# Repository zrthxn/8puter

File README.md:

# 8puter

This is a Homebrew 8-bit computer project, using mostly simple modern parts.
Based on the legendary MOS6502 processor, we are using the modern CMOS version made by WDC. Basically an exercise in computer architechture. I plan to get this manufactured into a PCB and assemble myself into a working computer. 

Please feel free to leave reviews/sanity checks from people who have done this sort of thing before, or know something about this, in the [issues](/issues).  

## Preview

Here is a picture of a 3D model of the completed PCB.

<p align="center" style="text-align: center; font-size: larger; font-weight: 600;">
// 
<a href="plots/8puter.pdf">Schematic</a> / 
<a href="plots/8puter.csv">Bill of Materials</a> 
//
</p>

## My Goals

The main thing I want to be able to do with this SBC is to program it with itself. This means having some way to input text from a keyboard and display it to some kind of screen/output device, and I've chosen a VGA monitor for this. I'm not trying to keep this compatible with the ROMs/BIOSs or code of old but I want to be able to write my own, preferably on the machine itself. 
Also, I dont want to use discrete logic for everything since I have some experience with trying to make that work. I'm also not necessarily using all DIP chips because of lack space, and going SMD isnt that much of a problem.

To store programs on a sort of "disk", I thought I need to add some sort of serial interface which can talk to a microSD card, such that the computer can use it as storage. This is accomplished via SPI. 
The peripheral interface talks to a USB controller and *should* be able to use a USB keyboard as input device. This idea was taken from the schematic of the [SBC dev board that WDC sells](https://wdc65xx.com/Single-Board-Computers/w65c02sxb/).

The video signal is being generated by a microcontroller because I thought that's probably the easiest way to get it working without worrying about a lot of VGA signal timing. This MCU is fast enough to generate a 640x480 screen and has enough memory to store the framebuffer and its the only *cheat* I've used. Some more details are in my schematic

### Main Parts

**uProcessor:** W65C02S  
**ROM and RAM:** AT28C256 and AS6C62256, both 32K  
**VIA:** W65C22  
**USB I/f:** FT245RL  
**Video:** PIC32MX270 uController

## Manufacturing

So after quite a while, I have finally got this PCB manufactured and it came out better than I had imagined.
I was having trouble finding a local PCB maker who had the right capabilities and would manufacture this board at a small scale. 
Then I found Robu.in and their manufacturing service. I'm not sure if they've been doing this for a while but I never knew about them.

The board files are ready to send to a manufacturer of your choice as they are. You can find the gerbers in a ZIP and just fire them off. 
I recommend Robu.in if you're in India. Otherwise I'd recommend PCBWay.com

See the [Releases](https://github.com/zrthxn/8puter/releases) for updates.

## Resources

Some great resources I found for this project, including those from people who have done this sort of thing before.

- [Ben Eater's Excellent Videos](https://www.youtube.com/watch?v=LnzuMJLZRdU&list=PLowKtXNTBypFbtuVMUVXNR0z1mu7dp7eH)
- [George Foot's videos](https://www.youtube.com/watch?v=EC1Ous1zT5w&list=PLWKtKD_FaUF6IsFc1maERpOwWM2hrOM3b)
- [forum.6502.org](http://forum.6502.org/)
- [WDC's own SBC board schematic](https://wdc65xx.com/Single-Board-Computers/w65c02sxb/)
- [6052 Primer](http://wilsonminesco.com/6502primer) on how to get started building your own, especially the [address decode](http://wilsonminesco.com/6502primer/addr_decoding.html) section
- [6502.org: Homebuilt Projects](http://www.6502.org/homebuilt)
- [This guy's breadboard computer](https://www.youtube.com/watch?v=sdFXc0Rkpvc&list=PLdGm_pyUmoII9D16mzw-XsJjHKi3f1kqT) which is based on the (later) 65816 processor, but has some great ideas.

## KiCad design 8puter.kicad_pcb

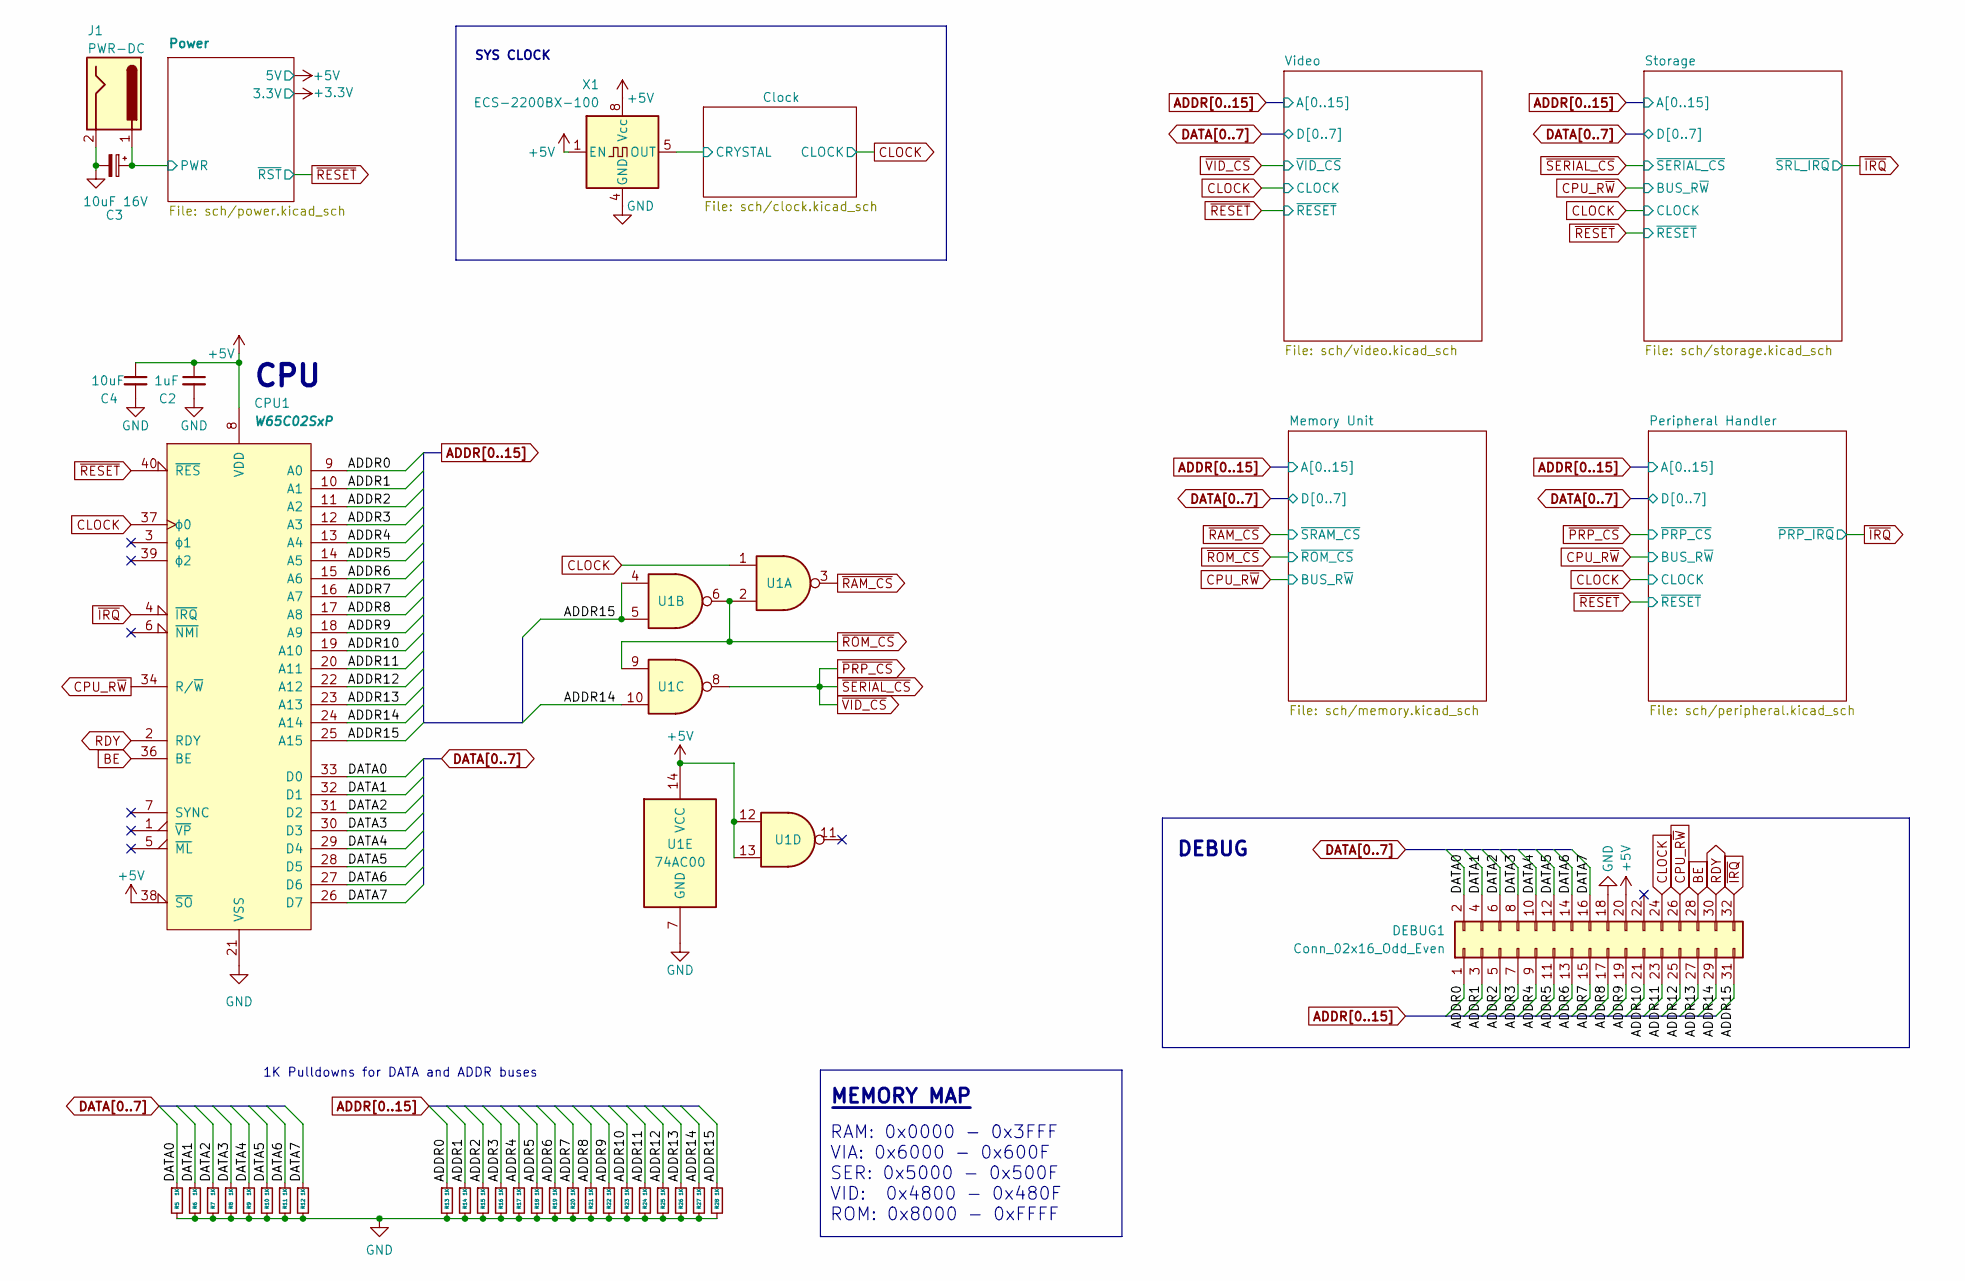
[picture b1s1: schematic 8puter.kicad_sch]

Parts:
C2: 1uF; C_0805_2012Metric
C3: 10uF 16V; CP_Radial_D5.0mm_P2.50mm
C4: 10uF; C_0805_2012Metric
CPU1: W65C02SxP; DIP-40_W15.24mm_LongPads
DEBUG1: Conn_02x16_Odd_Even; PinHeader_2x16_P2.54mm_Vertical
J1: PWR-DC; BarrelJack_CUI_PJ-063AH_Horizontal
R5, R6, R7, R8, R9, R10, R11, R12, R13, R14, R15, R16, R17, R18, R19, R20, R21, R22, R23, R24, R25, R26, R27, R28: 1K; R_0805_2012Metric
U1: 74AC00; TSSOP-14_4.4x5mm_P0.65mm
X1: ECS-2200BX-100; Oscillator_DIP-8

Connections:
+5V: C2.1, C4.1, CPU1.8 (VDD), CPU1.38 (~SO), DEBUG1.20, U1.12, U1.13, U1.14 (VCC), X1.1 (EN), X1.8 (Vcc); also elsewhere on the board
/Clock/CRYSTAL: X1.5 (OUT); also elsewhere on the board
/Power/PWR: C3.1, J1.1; also elsewhere on the board
ADDR0: CPU1.9 (A0), DEBUG1.1, R13.1; also elsewhere on the board
ADDR1: CPU1.10 (A1), DEBUG1.3, R14.1; also elsewhere on the board
ADDR2: CPU1.11 (A2), DEBUG1.5, R15.1; also elsewhere on the board
ADDR3: CPU1.12 (A3), DEBUG1.7, R16.1; also elsewhere on the board
ADDR4: CPU1.13 (A4), DEBUG1.9, R17.1; also elsewhere on the board
ADDR5: CPU1.14 (A5), DEBUG1.11, R18.1; also elsewhere on the board
ADDR6: CPU1.15 (A6), DEBUG1.13, R19.1; also elsewhere on the board
ADDR7: CPU1.16 (A7), DEBUG1.15, R20.1; also elsewhere on the board
ADDR8: CPU1.17 (A8), DEBUG1.17, R21.1; also elsewhere on the board
ADDR9: CPU1.18 (A9), DEBUG1.19, R22.1; also elsewhere on the board
ADDR10: CPU1.19 (A10), DEBUG1.21, R23.1; also elsewhere on the board
ADDR11: CPU1.20 (A11), DEBUG1.23, R24.1; also elsewhere on the board
ADDR12: CPU1.22 (A12), DEBUG1.25, R25.1; also elsewhere on the board
ADDR13: CPU1.23 (A13), DEBUG1.27, R26.1; also elsewhere on the board
ADDR14: CPU1.24 (A14), DEBUG1.29, R27.1, U1.10; also elsewhere on the board
ADDR15: CPU1.25 (A15), DEBUG1.31, R28.1, U1.4, U1.5
BE: CPU1.36 (BE), DEBUG1.28
CLOCK: CPU1.37 (ϕ0), DEBUG1.24, U1.1; also elsewhere on the board
CPU_R~W: CPU1.34 (R/~W), DEBUG1.26; also elsewhere on the board
DATA0: CPU1.33 (D0), DEBUG1.2, R5.1; also elsewhere on the board
DATA1: CPU1.32 (D1), DEBUG1.4, R6.1; also elsewhere on the board
DATA2: CPU1.31 (D2), DEBUG1.6, R7.1; also elsewhere on the board
DATA3: CPU1.30 (D3), DEBUG1.8, R8.1; also elsewhere on the board
DATA4: CPU1.29 (D4), DEBUG1.10, R9.1; also elsewhere on the board
DATA5: CPU1.28 (D5), DEBUG1.12, R10.1; also elsewhere on the board
DATA6: CPU1.27 (D6), DEBUG1.14, R11.1; also elsewhere on the board
DATA7: CPU1.26 (D7), DEBUG1.16, R12.1; also elsewhere on the board
RDY: CPU1.2 (RDY), DEBUG1.30
~IRQ: CPU1.4 (~IRQ), DEBUG1.32; also elsewhere on the board
~PRP_CS: U1.8; also elsewhere on the board
~RAM_CS: U1.3; also elsewhere on the board
~RESET: CPU1.40 (~RES); also elsewhere on the board
~ROM_CS: U1.2, U1.6, U1.9; also elsewhere on the board

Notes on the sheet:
SYS CLOCK
DEBUG
RAM: 0x0000 - 0x3FFF VIA: 0x6000 - 0x600F SER: 0x5000 - 0x500F VID: 0x4800 - 0x480F ROM: 0x8000 - 0xFFFF
MEMORY MAP ~{ }
1K Pulldowns for DATA and ADDR buses
CPU

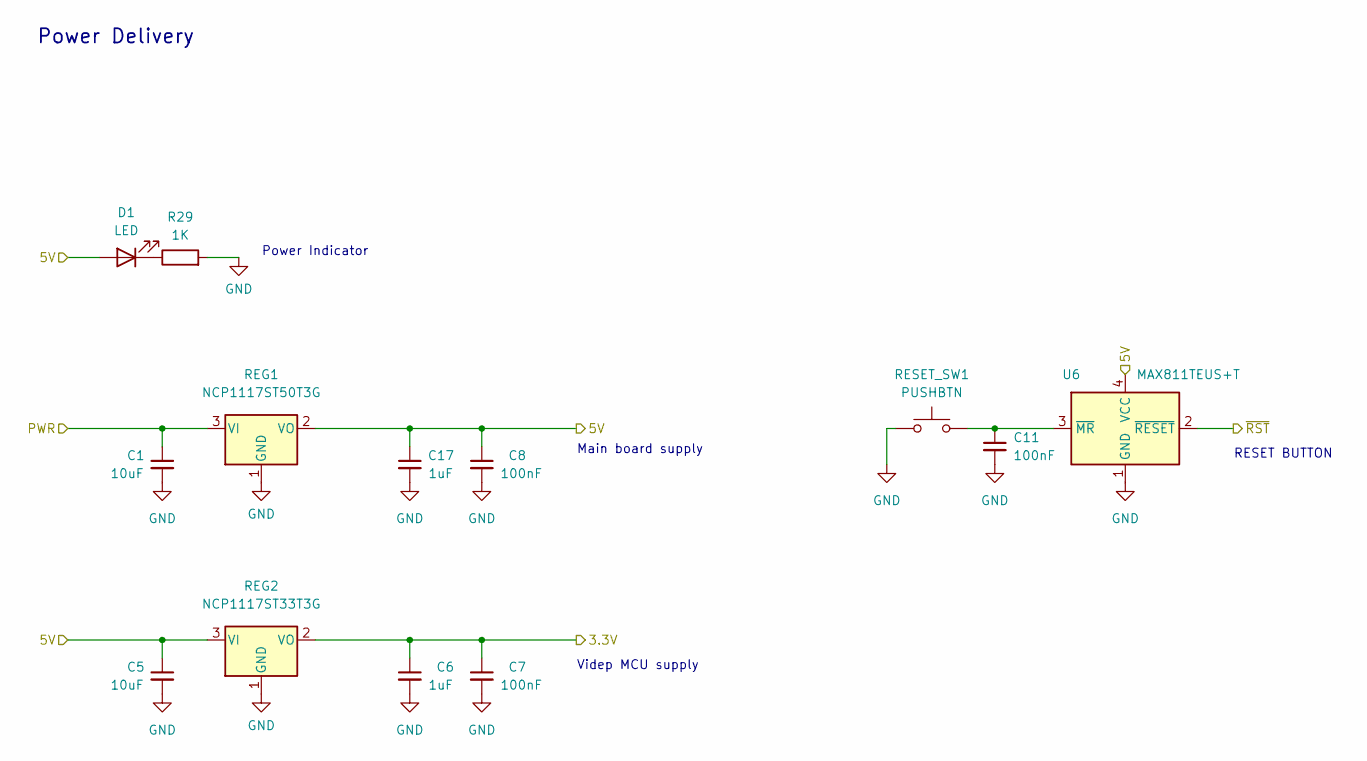
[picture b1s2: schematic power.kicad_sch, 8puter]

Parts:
C1, C5: 10uF; C_0805_2012Metric
C6, C17: 1uF; C_0805_2012Metric
C7, C8, C11: 100nF; C_0805_2012Metric
D1: LED; LED_0805_2012Metric
R29: 1K; R_0805_2012Metric
REG1: NCP1117ST50T3G; SOT-223-3_TabPin2
REG2: NCP1117ST33T3G; SOT-223-3_TabPin2
RESET_SW1: PUSHBTN; SW_PUSH_6mm_H13mm
U6: MAX811TEUS+T; SOT-143

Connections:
+3V3: C6.1, C7.1, REG2.2 (VO); also elsewhere on the board
+5V: C5.1, C8.1, C17.1, D1.2 (A), REG1.2 (VO), REG2.3 (VI), U6.4 (VCC); also elsewhere on the board
/Power/PWR: C1.1, REG1.3 (VI); also elsewhere on the board
unnamed: C11.1, RESET_SW1.2, U6.3 (~MR)
unnamed: D1.1 (K), R29.1
~RESET: U6.2 (~RESET); also elsewhere on the board

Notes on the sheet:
Power Delivery
RESET BUTTON
Videp MCU supply
Power Indicator
Main board supply

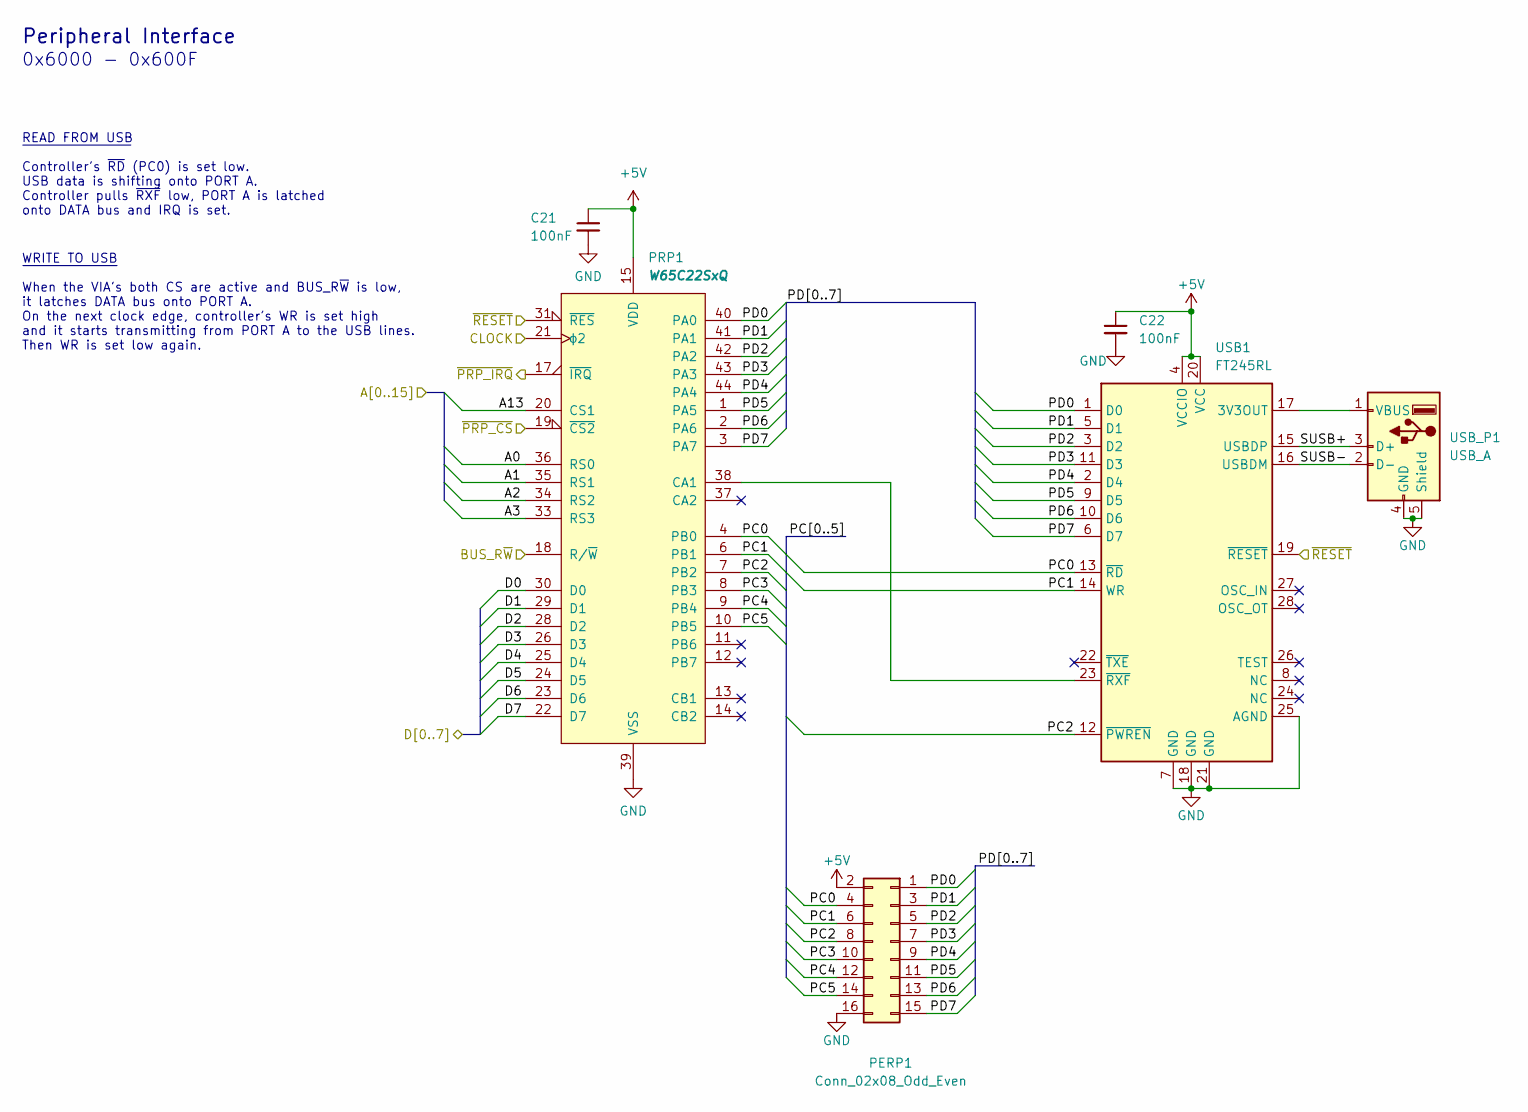
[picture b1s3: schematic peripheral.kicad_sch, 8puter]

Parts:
C21, C22: 100nF; C_0805_2012Metric
PERP1: Conn_02x08_Odd_Even; PinHeader_2x08_P2.54mm_Vertical
PRP1: W65C22SxQ; PQFP-44_10x10mm_P0.8mm
USB1: FT245RL; SSOP-28_5.3x10.2mm_P0.65mm
USB_P1: USB_A; USB_A_TE_292303-7_Horizontal

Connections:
+5V: C21.1, C22.1, PERP1.2, PRP1.15 (VDD), USB1.4 (VCCIO), USB1.20 (VCC); also elsewhere on the board
/Peripheral Handler/PC0: PERP1.4, PRP1.4 (PB0), USB1.13 (~RD)
/Peripheral Handler/PC1: PERP1.6, PRP1.6 (PB1), USB1.14 (WR)
/Peripheral Handler/PC2: PERP1.8, PRP1.7 (PB2), USB1.12 (~PWREN)
/Peripheral Handler/PC3: PERP1.10, PRP1.8 (PB3)
/Peripheral Handler/PC4: PERP1.12, PRP1.9 (PB4)
/Peripheral Handler/PC5: PERP1.14, PRP1.10 (PB5)
/Peripheral Handler/PD0: PERP1.1, PRP1.40 (PA0), USB1.1 (D0)
/Peripheral Handler/PD1: PERP1.3, PRP1.41 (PA1), USB1.5 (D1)
/Peripheral Handler/PD2: PERP1.5, PRP1.42 (PA2), USB1.3 (D2)
/Peripheral Handler/PD3: PERP1.7, PRP1.43 (PA3), USB1.11 (D3)
/Peripheral Handler/PD4: PERP1.9, PRP1.44 (PA4), USB1.2 (D4)
/Peripheral Handler/PD5: PERP1.11, PRP1.1 (PA5), USB1.9 (D5)
/Peripheral Handler/PD6: PERP1.13, PRP1.2 (PA6), USB1.10 (D6)
/Peripheral Handler/PD7: PERP1.15, PRP1.3 (PA7), USB1.6 (D7)
/Peripheral Handler/SUSB+: USB1.15 (USBDP), USB_P1.3 (D+)
/Peripheral Handler/SUSB-: USB1.16 (USBDM), USB_P1.2 (D-)
ADDR0: PRP1.36 (RS0); also elsewhere on the board
ADDR1: PRP1.35 (RS1); also elsewhere on the board
ADDR2: PRP1.34 (RS2); also elsewhere on the board
ADDR3: PRP1.33 (RS3); also elsewhere on the board
ADDR13: PRP1.20 (CS1); also elsewhere on the board
CLOCK: PRP1.21 (ϕ2); also elsewhere on the board
CPU_R~W: PRP1.18 (R/~W); also elsewhere on the board
DATA0: PRP1.30 (D0); also elsewhere on the board
DATA1: PRP1.29 (D1); also elsewhere on the board
DATA2: PRP1.28 (D2); also elsewhere on the board
DATA3: PRP1.26 (D3); also elsewhere on the board
DATA4: PRP1.25 (D4); also elsewhere on the board
DATA5: PRP1.24 (D5); also elsewhere on the board
DATA6: PRP1.23 (D6); also elsewhere on the board
DATA7: PRP1.22 (D7); also elsewhere on the board
unnamed: PRP1.38 (CA1), USB1.23 (~RXF)
unnamed: USB1.17 (3V3OUT), USB_P1.1 (VBUS)
~IRQ: PRP1.17 (~IRQ); also elsewhere on the board
~PRP_CS: PRP1.19 (~CS2); also elsewhere on the board
~RESET: PRP1.31 (~RES), USB1.19 (~RESET); also elsewhere on the board

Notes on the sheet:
0x6000 - 0x600F
Peripheral Interface
WRITE TO USB ~{ } When the VIA's both CS are active and BUS_R~{W} is low, it latches DATA bus onto PORT A. On the next clock edge, controller's WR is set high and it starts transmitting from PORT A to the USB lines. Then WR is set low again.
READ FROM USB ~{ } Controller's ~{RD} (PC0) is set low. USB data is shifting onto PORT A. Controller pulls ~{RXF} low, PORT A is latched onto DATA bus and IRQ is set.

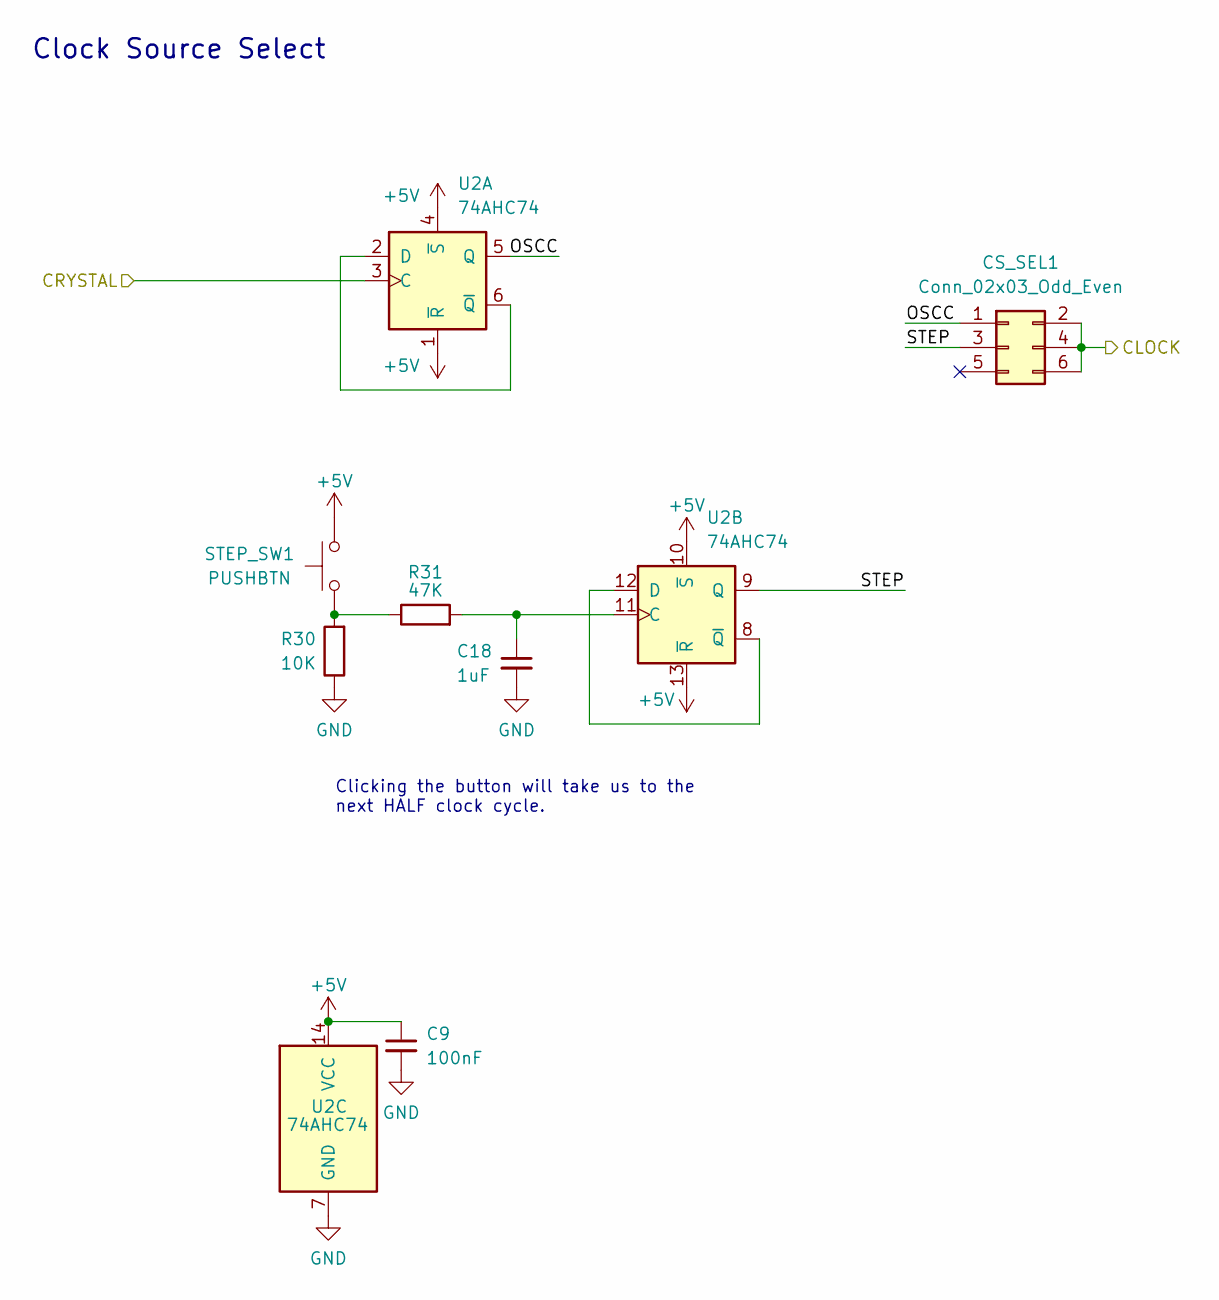
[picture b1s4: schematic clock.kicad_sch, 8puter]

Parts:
C9: 100nF; C_0805_2012Metric
C18: 1uF; C_0805_2012Metric
CS_SEL1: Conn_02x03_Odd_Even; PinHeader_2x03_P2.54mm_Vertical
R30: 10K; R_0805_2012Metric
R31: 47K; R_0805_2012Metric
STEP_SW1: PUSHBTN; SW_PUSH_6mm_H13mm
U2: 74AHC74; TSSOP-14_4.4x5mm_P0.65mm

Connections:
+5V: C9.1, STEP_SW1.2, U2.1 (~R), U2.4 (~S), U2.10 (~S), U2.13 (~R), U2.14 (VCC); also elsewhere on the board
/Clock/CRYSTAL: U2.3 (C); also elsewhere on the board
/Clock/OSCC: CS_SEL1.1, U2.5 (Q)
/Clock/STEP: CS_SEL1.3, U2.9 (Q)
CLOCK: CS_SEL1.2, CS_SEL1.4, CS_SEL1.6; also elsewhere on the board
unnamed: C18.1, R31.2, U2.11 (C)
unnamed: R30.2, R31.1, STEP_SW1.1
unnamed: U2.2 (D), U2.6 (~Q)
unnamed: U2.8 (~Q), U2.12 (D)

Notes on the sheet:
Clicking the button will take us to the next HALF clock cycle.
Clock Source Select

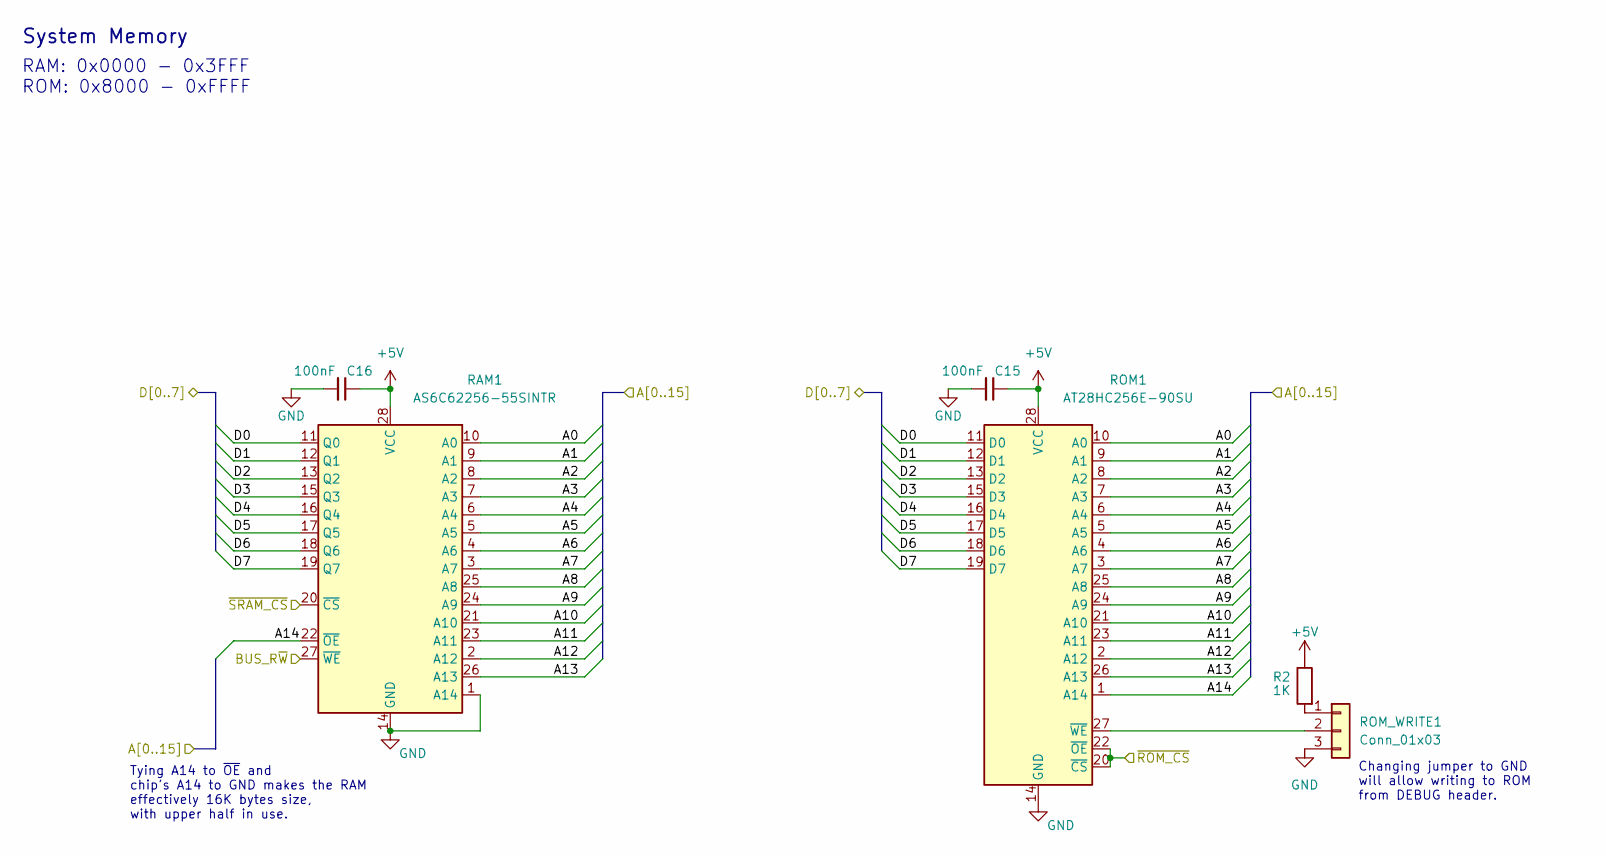
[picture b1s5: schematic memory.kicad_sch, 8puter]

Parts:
C15, C16: 100nF; C_0805_2012Metric
R2: 1K; R_0805_2012Metric
RAM1: AS6C62256-55SINTR; SOIC-28W_7.5x17.9mm_P1.27mm
ROM1: AT28HC256E-90SU; SOIC-28W_7.5x17.9mm_P1.27mm
ROM_WRITE1: Conn_01x03; PinHeader_1x03_P2.54mm_Vertical

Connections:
+5V: C15.1, C16.1, R2.1, RAM1.28 (VCC), ROM1.28 (VCC); also elsewhere on the board
ADDR0: RAM1.10 (A0), ROM1.10 (A0); also elsewhere on the board
ADDR1: RAM1.9 (A1), ROM1.9 (A1); also elsewhere on the board
ADDR2: RAM1.8 (A2), ROM1.8 (A2); also elsewhere on the board
ADDR3: RAM1.7 (A3), ROM1.7 (A3); also elsewhere on the board
ADDR4: RAM1.6 (A4), ROM1.6 (A4); also elsewhere on the board
ADDR5: RAM1.5 (A5), ROM1.5 (A5); also elsewhere on the board
ADDR6: RAM1.4 (A6), ROM1.4 (A6); also elsewhere on the board
ADDR7: RAM1.3 (A7), ROM1.3 (A7); also elsewhere on the board
ADDR8: RAM1.25 (A8), ROM1.25 (A8); also elsewhere on the board
ADDR9: RAM1.24 (A9), ROM1.24 (A9); also elsewhere on the board
ADDR10: RAM1.21 (A10), ROM1.21 (A10); also elsewhere on the board
ADDR11: RAM1.23 (A11), ROM1.23 (A11); also elsewhere on the board
ADDR12: RAM1.2 (A12), ROM1.2 (A12); also elsewhere on the board
ADDR13: RAM1.26 (A13), ROM1.26 (A13); also elsewhere on the board
ADDR14: RAM1.22 (~OE), ROM1.1 (A14); also elsewhere on the board
CPU_R~W: RAM1.27 (~WE); also elsewhere on the board
DATA0: RAM1.11 (Q0), ROM1.11 (D0); also elsewhere on the board
DATA1: RAM1.12 (Q1), ROM1.12 (D1); also elsewhere on the board
DATA2: RAM1.13 (Q2), ROM1.13 (D2); also elsewhere on the board
DATA3: RAM1.15 (Q3), ROM1.15 (D3); also elsewhere on the board
DATA4: RAM1.16 (Q4), ROM1.16 (D4); also elsewhere on the board
DATA5: RAM1.17 (Q5), ROM1.17 (D5); also elsewhere on the board
DATA6: RAM1.18 (Q6), ROM1.18 (D6); also elsewhere on the board
DATA7: RAM1.19 (Q7), ROM1.19 (D7); also elsewhere on the board
unnamed: R2.2, ROM_WRITE1.1
unnamed: ROM1.27 (~WE), ROM_WRITE1.2
~RAM_CS: RAM1.20 (~CS); also elsewhere on the board
~ROM_CS: ROM1.20 (~CS), ROM1.22 (~OE); also elsewhere on the board

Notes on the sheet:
RAM: 0x0000 - 0x3FFF ROM: 0x8000 - 0xFFFF
System Memory
Tying A14 to ~{OE} and chip's A14 to GND makes the RAM effectively 16K bytes size, with upper half in use.
Changing jumper to GND will allow writing to ROM from DEBUG header.

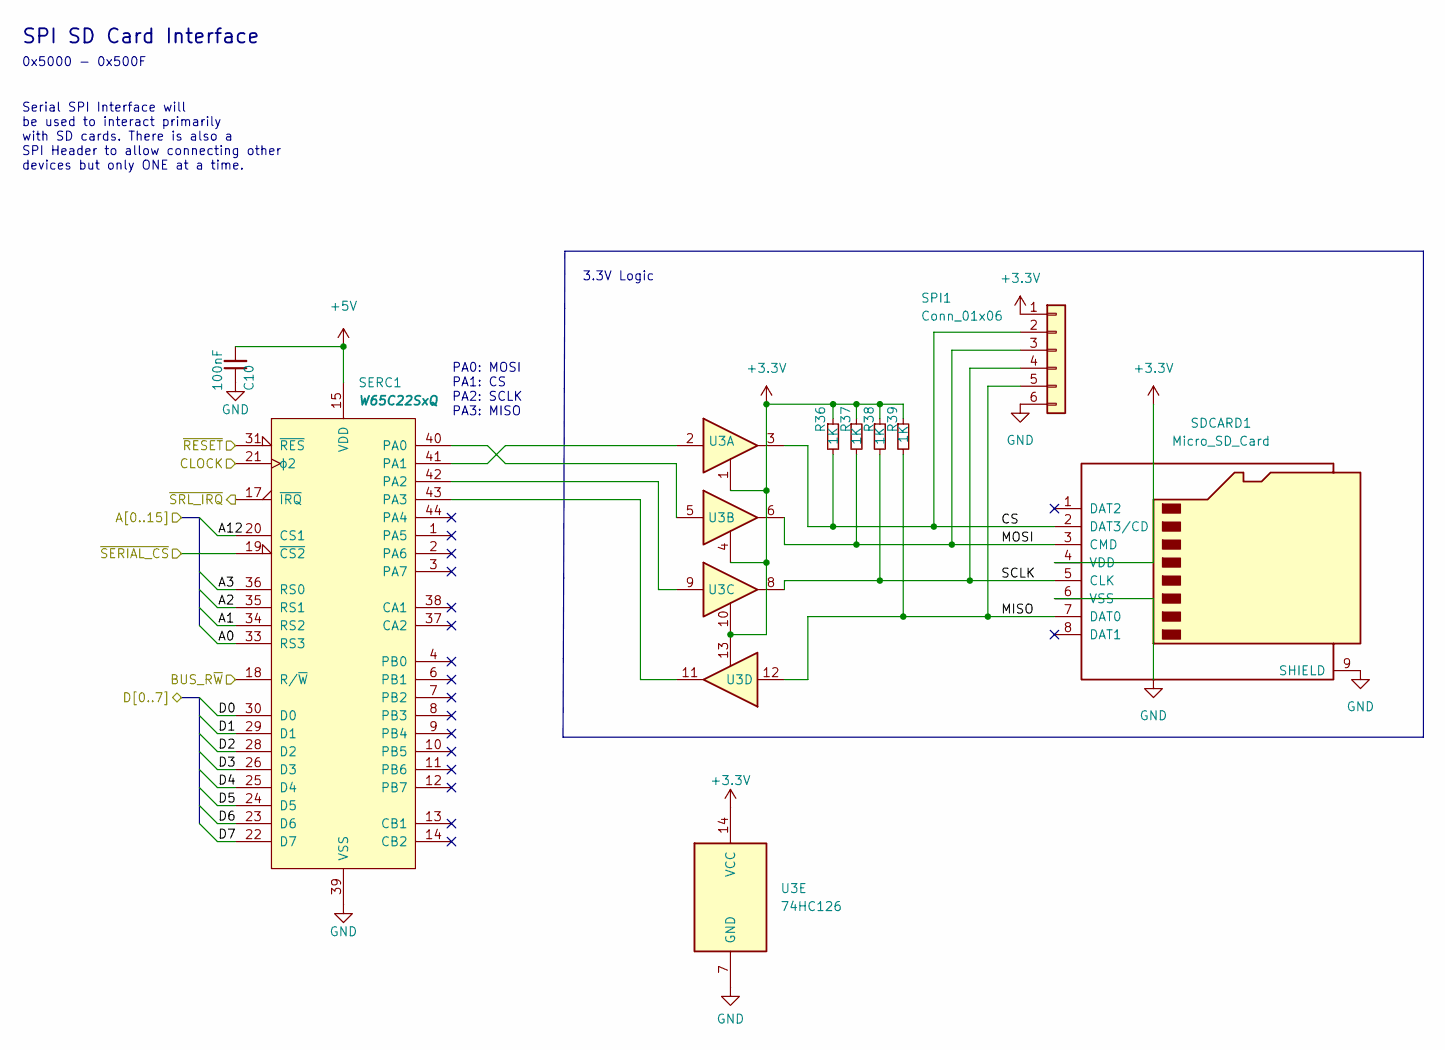
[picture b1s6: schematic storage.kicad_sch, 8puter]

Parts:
C10: 100nF; C_0805_2012Metric
R36, R37, R38, R39: 1K; R_0805_2012Metric
SDCARD1: Micro_SD_Card; microSD_HC_Molex_104031-0811
SERC1: W65C22SxQ; PQFP-44_10x10mm_P0.8mm
SPI1: Conn_01x06; PinHeader_1x06_P2.54mm_Vertical
U3: 74HC126; SOIC-14_3.9x8.7mm_P1.27mm

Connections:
+3V3: R36.1, R37.1, R38.1, R39.1, SDCARD1.4 (VDD), SPI1.1, U3.1, U3.4, U3.10, U3.13, U3.14 (VCC); also elsewhere on the board
+5V: C10.2, SERC1.15 (VDD); also elsewhere on the board
/Storage/CS: R36.2, SDCARD1.2 (DAT3/CD), SPI1.2, U3.3
/Storage/MISO: R39.2, SDCARD1.7 (DAT0), SPI1.5, U3.12
/Storage/MOSI: R37.2, SDCARD1.3 (CMD), SPI1.3, U3.6
/Storage/SCLK: R38.2, SDCARD1.5 (CLK), SPI1.4, U3.8
ADDR0: SERC1.33 (RS3); also elsewhere on the board
ADDR1: SERC1.34 (RS2); also elsewhere on the board
ADDR2: SERC1.35 (RS1); also elsewhere on the board
ADDR3: SERC1.36 (RS0); also elsewhere on the board
ADDR12: SERC1.20 (CS1); also elsewhere on the board
CLOCK: SERC1.21 (ϕ2); also elsewhere on the board
CPU_R~W: SERC1.18 (R/~W); also elsewhere on the board
DATA0: SERC1.30 (D0); also elsewhere on the board
DATA1: SERC1.29 (D1); also elsewhere on the board
DATA2: SERC1.28 (D2); also elsewhere on the board
DATA3: SERC1.26 (D3); also elsewhere on the board
DATA4: SERC1.25 (D4); also elsewhere on the board
DATA5: SERC1.24 (D5); also elsewhere on the board
DATA6: SERC1.23 (D6); also elsewhere on the board
DATA7: SERC1.22 (D7); also elsewhere on the board
unnamed: SERC1.40 (PA0), U3.5
unnamed: SERC1.41 (PA1), U3.2
unnamed: SERC1.42 (PA2), U3.9
unnamed: SERC1.43 (PA3), U3.11
~IRQ: SERC1.17 (~IRQ); also elsewhere on the board
~PRP_CS: SERC1.19 (~CS2); also elsewhere on the board
~RESET: SERC1.31 (~RES); also elsewhere on the board

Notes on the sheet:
SPI SD Card Interface
0x5000 - 0x500F
PA0: MOSI PA1: CS PA2: SCLK PA3: MISO
Serial SPI Interface will be used to interact primarily with SD cards. There is also a SPI Header to allow connecting other devices but only ONE at a time.
3.3V Logic

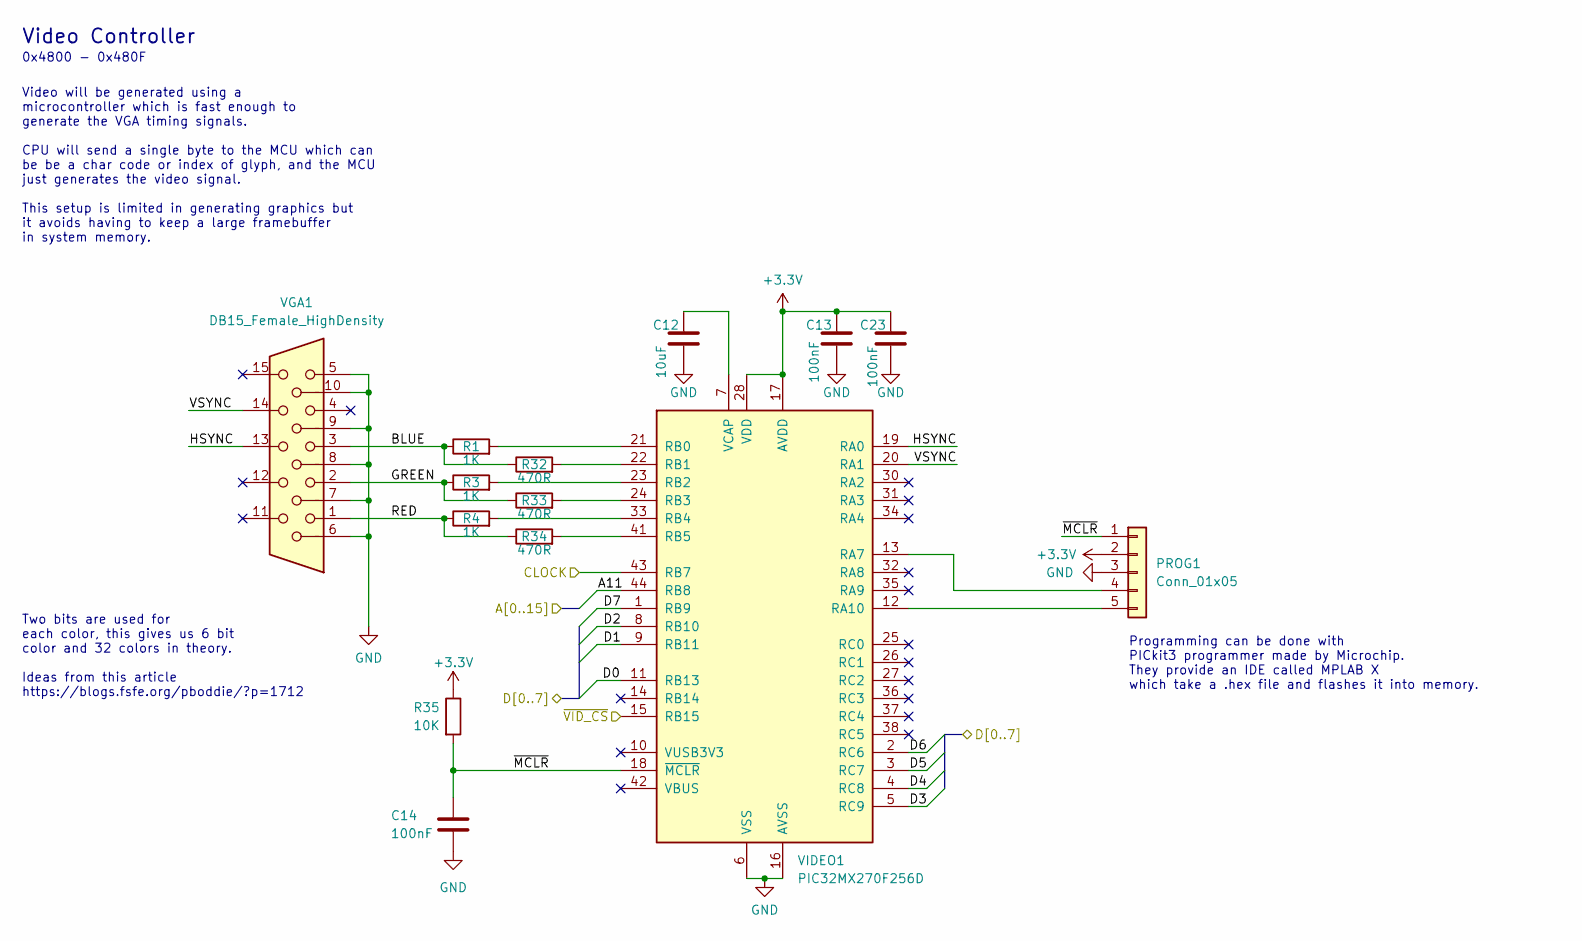
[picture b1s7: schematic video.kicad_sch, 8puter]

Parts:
C12: 10uF; C_0805_2012Metric
C13, C14, C23: 100nF; C_0805_2012Metric
PROG1: Conn_01x05; PinHeader_1x05_P2.54mm_Vertical
R1, R3, R4: 1K; R_0805_2012Metric
R32, R33, R34: 470R; R_0805_2012Metric
R35: 10K; R_0805_2012Metric
VGA1: DB15_Female_HighDensity; DSUB-15-HD_Female_Horizontal_P2.29x1.98mm_EdgePinOffset3.03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
VIDEO1: PIC32MX270F256D; TQFP-44_10x10mm_P0.8mm

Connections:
+3V3: C13.1, C23.1, PROG1.2, R35.1, VIDEO1.17 (AVDD), VIDEO1.28 (VDD), VIDEO1.40 (VDD); also elsewhere on the board
/Video/BLUE: R1.1, R32.1, VGA1.3
/Video/GREEN: R3.1, R33.1, VGA1.2
/Video/HSYNC: VGA1.13, VIDEO1.19 (RA0)
/Video/RED: R4.1, R34.1, VGA1.1
/Video/VSYNC: VGA1.14, VIDEO1.20 (RA1)
/Video/~MCLR: C14.1, PROG1.1, R35.2, VIDEO1.18 (~MCLR)
ADDR11: VIDEO1.44 (RB8); also elsewhere on the board
CLOCK: VIDEO1.43 (RB7); also elsewhere on the board
DATA0: VIDEO1.11 (RB13); also elsewhere on the board
DATA1: VIDEO1.9 (RB11); also elsewhere on the board
DATA2: VIDEO1.8 (RB10); also elsewhere on the board
DATA3: VIDEO1.5 (RC9); also elsewhere on the board
DATA4: VIDEO1.4 (RC8); also elsewhere on the board
DATA5: VIDEO1.3 (RC7); also elsewhere on the board
DATA6: VIDEO1.2 (RC6); also elsewhere on the board
DATA7: VIDEO1.1 (RB9); also elsewhere on the board
unnamed: C12.1, VIDEO1.7 (VCAP)
unnamed: PROG1.4, VIDEO1.13 (RA7)
unnamed: PROG1.5, VIDEO1.12 (RA10)
unnamed: R1.2, VIDEO1.21 (RB0)
unnamed: R3.2, VIDEO1.23 (RB2)
unnamed: R4.2, VIDEO1.33 (RB4)
unnamed: R32.2, VIDEO1.22 (RB1)
unnamed: R33.2, VIDEO1.24 (RB3)
unnamed: R34.2, VIDEO1.41 (RB5)
~PRP_CS: VIDEO1.15 (RB15); also elsewhere on the board

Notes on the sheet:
Video Controller
0x4800 - 0x480F
Two bits are used for each color, this gives us 6 bit color and 32 colors in theory. Ideas from this article https://blogs.fsfe.org/pboddie/?p=1712
Programming can be done with PICkit3 programmer made by Microchip. They provide an IDE called MPLAB X which take a .hex file and flashes it into memory.
Video will be generated using a microcontroller which is fast enough to generate the VGA timing signals. CPU will send a single byte to the MCU which can be be a char code or index of glyph, and the MCU just generates the video signal. This setup is limited in generating graphics but it avoids havi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

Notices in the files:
8puter.kicad_pcb:
GPL-3.0 Apr 2022
